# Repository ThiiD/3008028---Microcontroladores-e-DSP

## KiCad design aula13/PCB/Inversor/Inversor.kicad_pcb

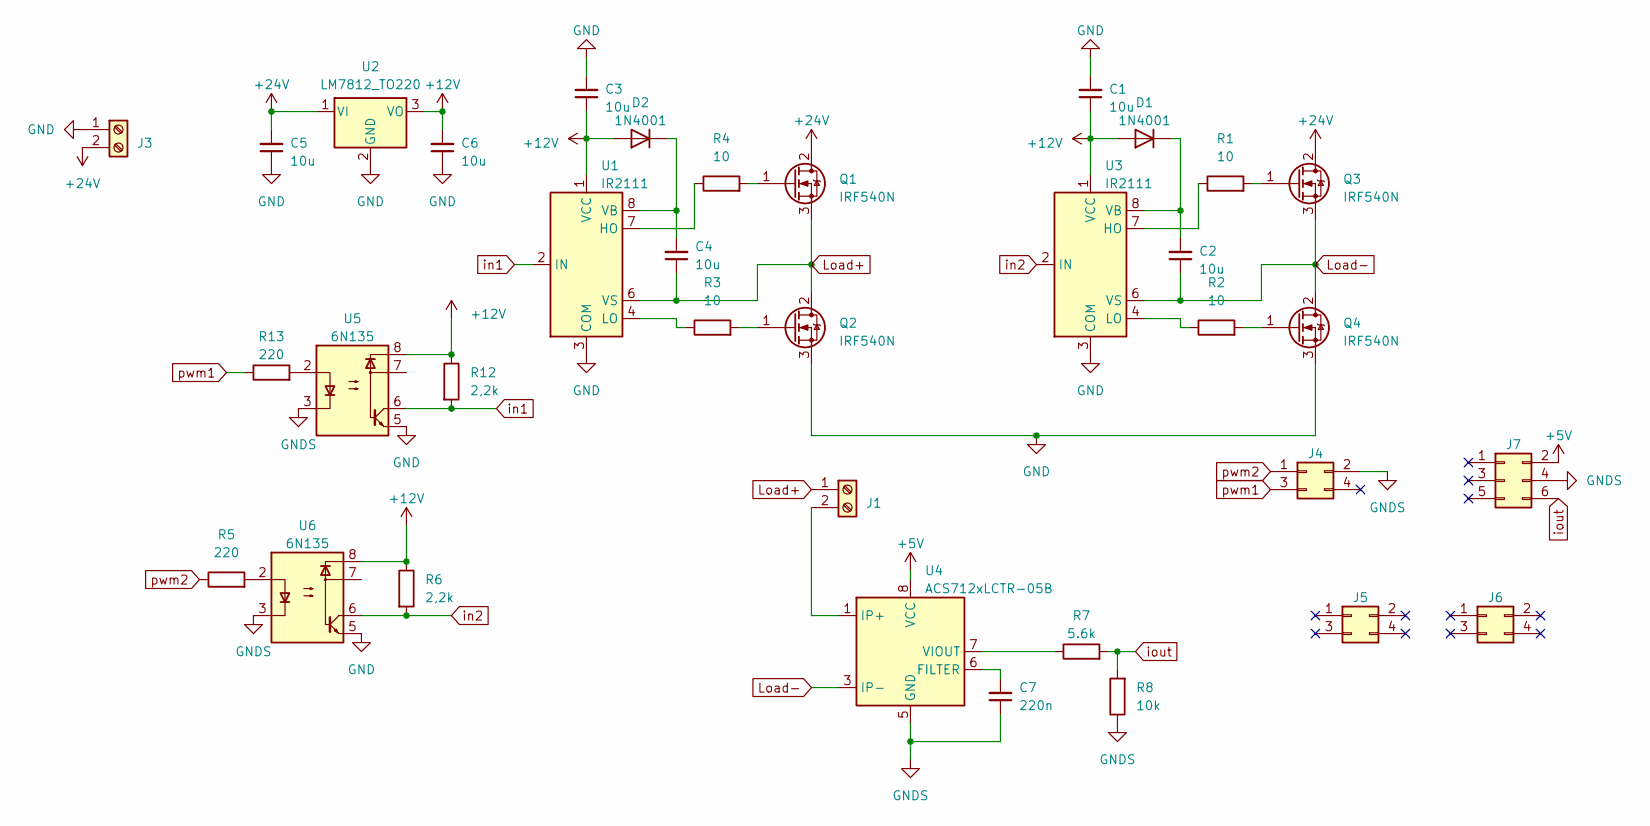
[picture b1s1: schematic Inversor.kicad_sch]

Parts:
C1, C2, C3, C4, C5, C6: 10u; C_1206_3216Metric
C7: 220n; C_1206_3216Metric
D1, D2: 1N4001; D_DO-41_SOD81_P10.16mm_Horizontal
J1, J3: Screw_Terminal_01x02; TerminalBlock_Altech_AK300-2_P5.00mm
J4, J5, J6: Conn_02x02_Odd_Even; PinHeader_2x02_P2.54mm_Vertical
J7: Conn_02x03_Odd_Even; PinHeader_2x03_P2.54mm_Vertical
Q1, Q2, Q3, Q4: IRF540N; TO-220-3_Vertical
R1, R2, R3, R4: 10; R_0805_2012Metric
R5, R13: 220; R_0805_2012Metric
R6, R12: 2,2k; R_0805_2012Metric
R7: 5.6k; R_0805_2012Metric
R8: 10k; R_0805_2012Metric
U1, U3: IR2111; DIP-8_W7.62mm_LongPads
U2: LM7812_TO220; TO-220-3_Vertical
U4: ACS712xLCTR-05B; SOIC-8_3.9x4.9mm_P1.27mm
U5, U6: 6N135; DIP-8_W7.62mm

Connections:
+5V: J7.2, U4.8 (VCC)
+15V: C1.1, C3.1, C6.2, D1.2 (A), D2.2 (A), R6.1, R12.1, U1.1 (VCC), U2.3 (VO), U3.1 (VCC), U5.8, U6.8
+24V: C5.2, J3.2, Q1.2 (D), Q3.2 (D), U2.1 (VI)
GND: C1.2, C3.2, C5.1, C6.1, J3.1, Q2.3 (S), Q4.3 (S), U1.3 (COM), U2.2 (GND), U3.3 (COM), U5.5, U6.5
GNDS: C7.1, J4.2, J7.4, R8.1, U4.5 (GND), U5.3, U6.3
Load+: C4.1, J1.1, Q1.3 (S), Q2.2 (D), U1.6 (VS)
Load-: C2.1, Q3.3 (S), Q4.2 (D), U3.6 (VS), U4.3 (IP-), U4.4 (IP-)
unnamed: C2.2, D1.1 (K), U3.8 (VB)
unnamed: C4.2, D2.1 (K), U1.8 (VB)
unnamed: J1.2, U4.1 (IP+), U4.2 (IP+)
unnamed: Q1.1 (G), R4.2
unnamed: Q2.1 (G), R3.2
unnamed: Q3.1 (G), R1.2
unnamed: Q4.1 (G), R2.2
unnamed: R5.2, U6.2
unnamed: R13.2, U5.2
unnamed: R4.1, U1.7 (HO)
unnamed: R3.1, U1.4 (LO)
unnamed: R1.1, U3.7 (HO)
unnamed: R2.1, U3.4 (LO)
unnamed: C7.2, U4.6 (FILTER)
unnamed: R7.1, U4.7 (VIOUT)
in1: R12.2, U1.2 (IN), U5.6
in2: R6.2, U3.2 (IN), U6.6
iout: J7.6, R7.2, R8.2
pwm1: J4.3, R13.1
pwm2: J4.1, R5.1

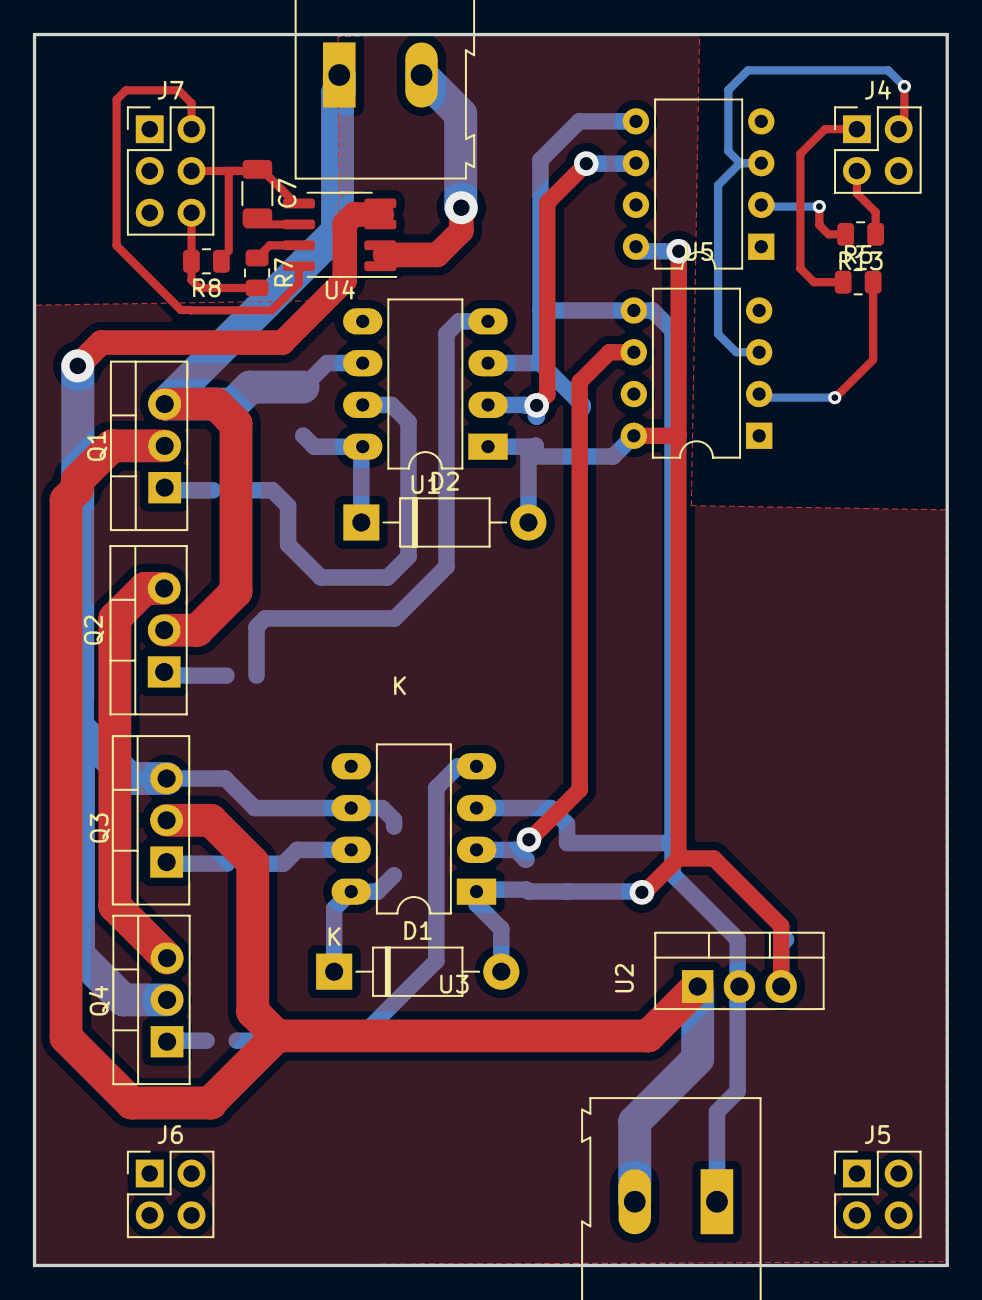
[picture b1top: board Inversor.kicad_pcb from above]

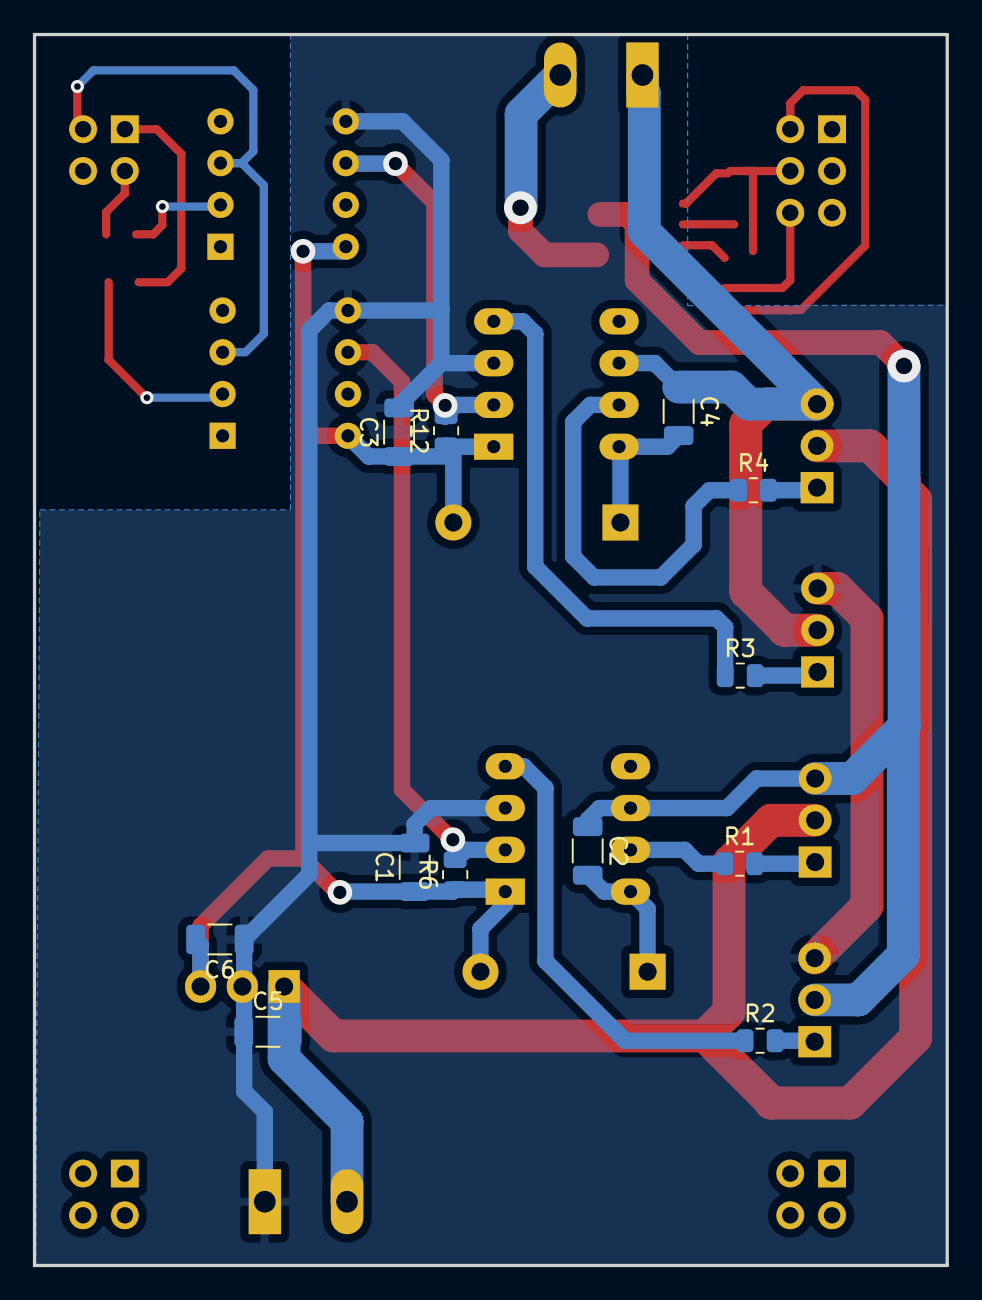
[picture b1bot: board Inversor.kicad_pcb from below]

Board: 2 copper layers, 55.5 x 74.8 mm, 35 parts (12 on the bottom side), 27 nets.

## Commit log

2023-11-06 Primeiro trabalho
    Inicio do primeiro trabalho.
2023-11-12 NF - Trabalho 2
    Trabalho 2 não finalizado
2023-11-13 Segundo Trabalho
    Segundo trabalho finalizado. Pequeno erro ao acrescentar a frequência da modulante do PWM.
2023-12-04 Terceiro Trabalho
    Filtragem sem DSPLib Funcionando.
